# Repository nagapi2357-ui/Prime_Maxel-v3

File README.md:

# Prime_Maxel-v3 — Experimental Torsion Resonator Network

> **⚠️ CORRIGENDUM (19 September 2026):** The results reported below have not been reproduced in a subsequent pre-registered replication experiment (Plan C) using pure sine waves. Seven of eight metrics returned null; the original effects are attributed to a harmonic confound from square-wave signal generation. See the [full corrigendum](https://github.com/nagapi2357-ui/pwt-v3-data/blob/main/CORRIGENDUM.md) for details. The original data and claims are preserved below for transparency.

~~First experimental evidence that prime-ratio frequency networks outperform composite-ratio networks in a physical resonator.~~

**Published:** [Zenodo DOI 10.5281/zenodo.20637347](https://doi.org/10.5281/zenodo.20637347)

## Overview

Prime_Maxel-v3 is a 12-cell torsion resonator ring built to test whether prime-ratio frequency relationships produce measurably different coupling behaviour compared to composite ratios. Each cell pairs a **SLG47004V GreenPAK** mixed-signal IC with an **LM324 op-amp**, connected via twin shared copper torsion traces on a 4-layer PCB fabricated by JLCPCB. An **Arduino Mega 2560** generates six independent square-wave channels using Timer1, fed into the ring through bodge wires. Output is captured on a **Rigol DS1054Z** oscilloscope and processed through a Python analysis pipeline.

Fifteen distinct frequency sets were tested across prime, composite, Fibonacci, zeta-zero, and coprimality configurations — producing the **Four-Factor Theory** of resonator coupling.

## Key Results (Original — See Corrigendum)

> ⚠️ These results have not been reproduced under controlled conditions. The effects are most likely due to odd-harmonic content in the square-wave signals, not the arithmetic properties of the frequency ratios. A [pre-registered replication](https://github.com/nagapi2357-ui/pwt-v3-data/blob/main/CORRIGENDUM.md) using pure sine waves returned null on amplitude, coherence, and cross-correlation.

- ~~**+28%**~~ peak spectral amplitude (prime vs composite ratios)
- ~~**+22%**~~ inter-channel coherence
- ~~**48% fewer**~~ intermodulation products
- **Superlinear** amplitude growth across 6 prime channels (320 → 1160 mV) — *not retested*
- **15 distinct frequency sets** tested → Four-Factor Theory
- Tusk-resonant set {1, 2, 3, 5, 6, 7} exceeds pure primes by **24%** — *not retested*
- Riemann zeta zeros resonate at **85–90%** of prime performance — *not retested*
- All integer divisors produce identical coupling power — **coprimality governs spectral quality** — *not retested*

## Board Images

| Top | Bottom |
|-----|--------|
|  |  |

## Architecture

```
Arduino Mega (Timer1) → 6× square-wave channels → bodge wires
    ↓
12× cells (SLG47004V + LM324) in circular ring
    ↓
TORSION_A (498 mm) / TORSION_B (601 mm) shared copper traces
    ↓
Rigol DS1054Z → Python analysis pipeline
```

## Repository Structure

- `arduino/` — All Arduino sketches (prime, composite, zeta zero, progressive, coprimality experiments, etc.)
- `Nagaπ Python Scripts/` — Analysis pipeline (rigol_capture.py, torsion_analyze.py, experiment_suite_analysis.py)
- `research/` — Experimental results, detailed write-ups per experiment, and the published paper
- `LTspice_Sim/` — SPICE simulations of the golden cell circuit
- `Go Configure/` — GreenPAK configuration files
- `docs/` — Board renders
- `Libraries/` — Custom KiCad symbols and footprints
- KiCad project files at root

## Companion Publications

- **Prime Resonance Theory:** DOI [10.5281/zenodo.20541350](https://doi.org/10.5281/zenodo.20541350)
- **The Tusk Series:** DOI [10.5281/zenodo.19852116](https://doi.org/10.5281/zenodo.19852116)
- **Rational Algebraic Superformula:** DOI [10.5281/zenodo.20512346](https://doi.org/10.5281/zenodo.20512346)
- **Prime Tree Architecture:** DOI [10.5281/zenodo.20609886](https://doi.org/10.5281/zenodo.20609886)

## License

- **Hardware** (KiCad files): [CERN-OHL-S v2](https://ohwr.org/cern_ohl_s_v2.txt)
- **Code** (Arduino/Python): [Apache 2.0](https://www.apache.org/licenses/LICENSE-2.0)
- **Research papers**: [CC BY-SA 4.0](https://creativecommons.org/licenses/by-sa/4.0/)

See [LICENSE](LICENSE) for details.

## Author

**Adrian Sutton** — [Tusk Innovations](https://github.com/nagapi2357-ui)

AI Research Contributor: **Nagaπ**

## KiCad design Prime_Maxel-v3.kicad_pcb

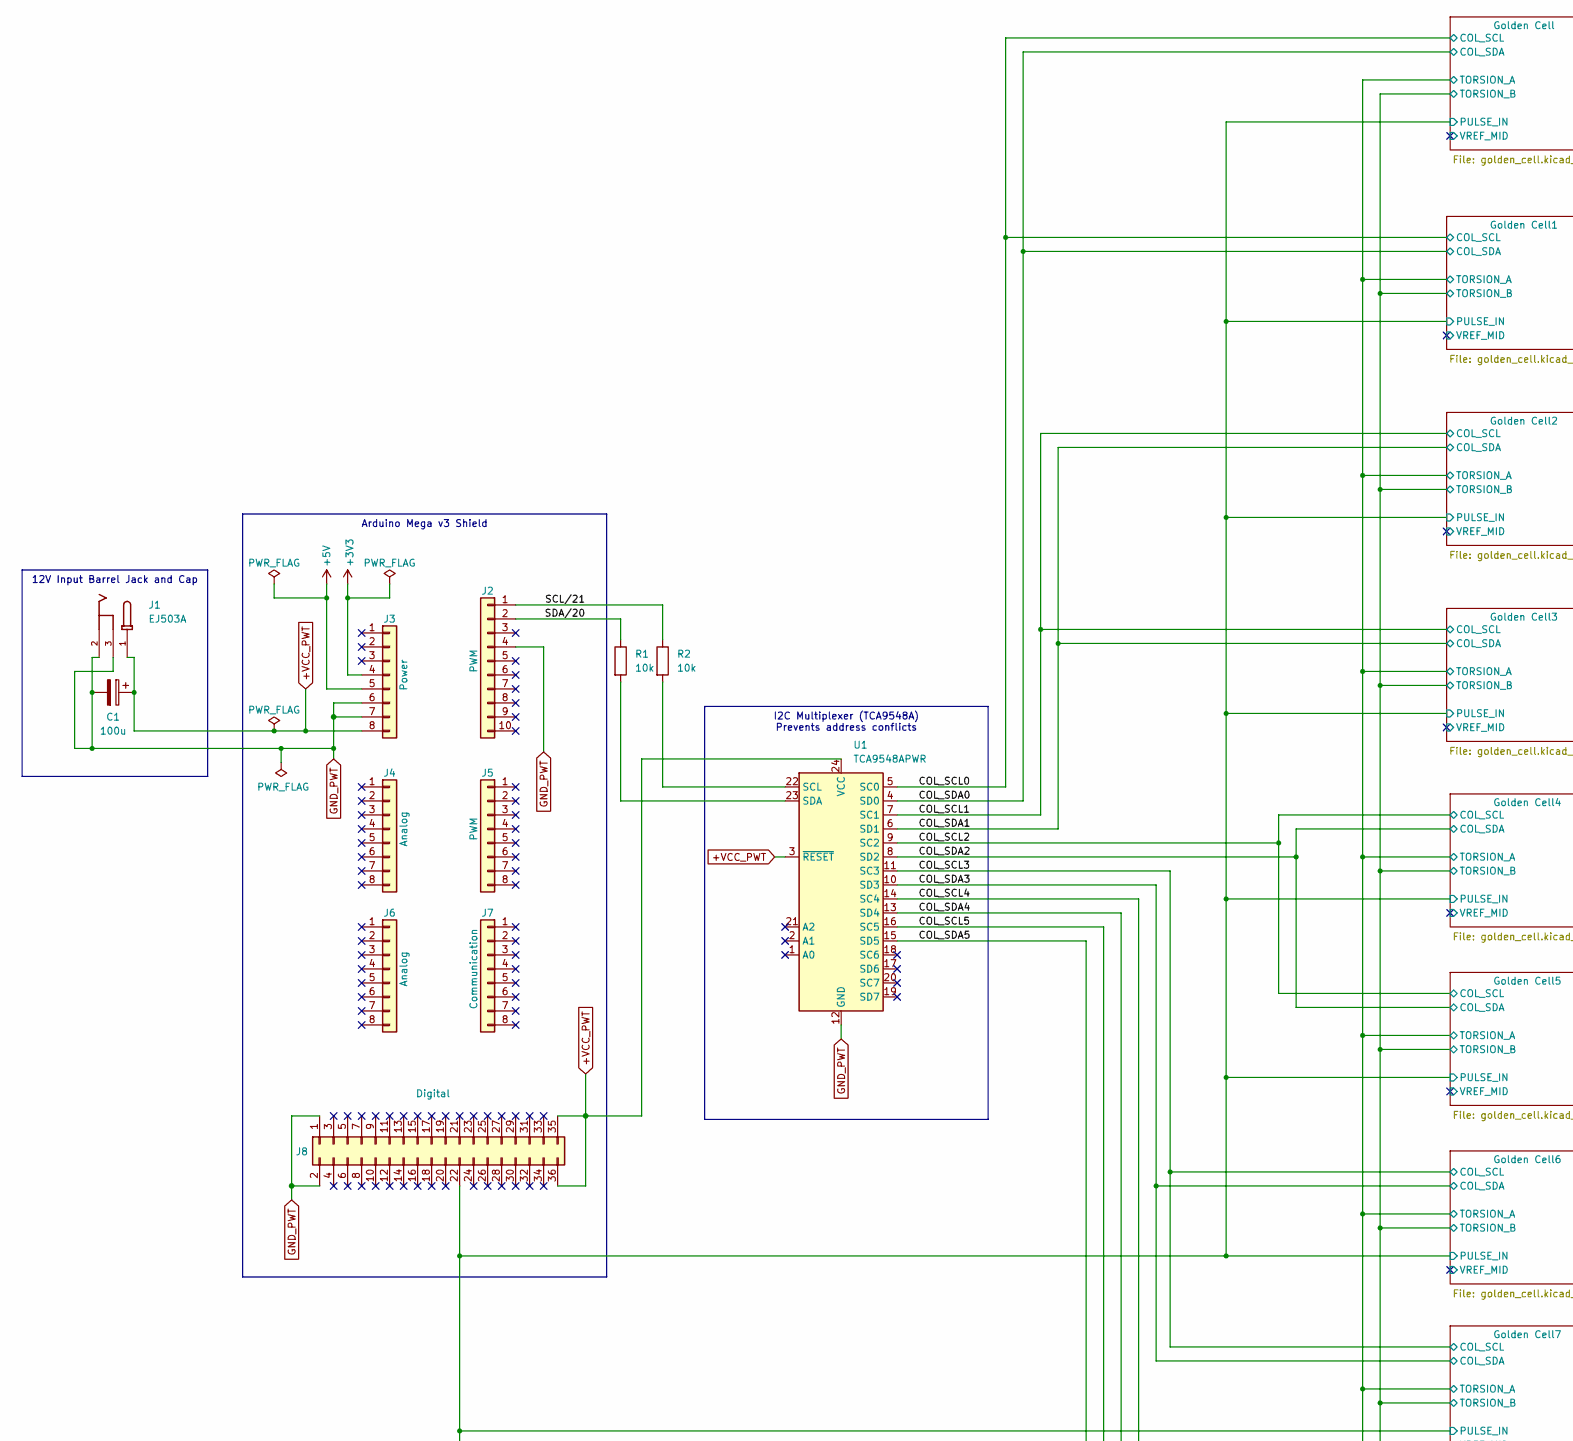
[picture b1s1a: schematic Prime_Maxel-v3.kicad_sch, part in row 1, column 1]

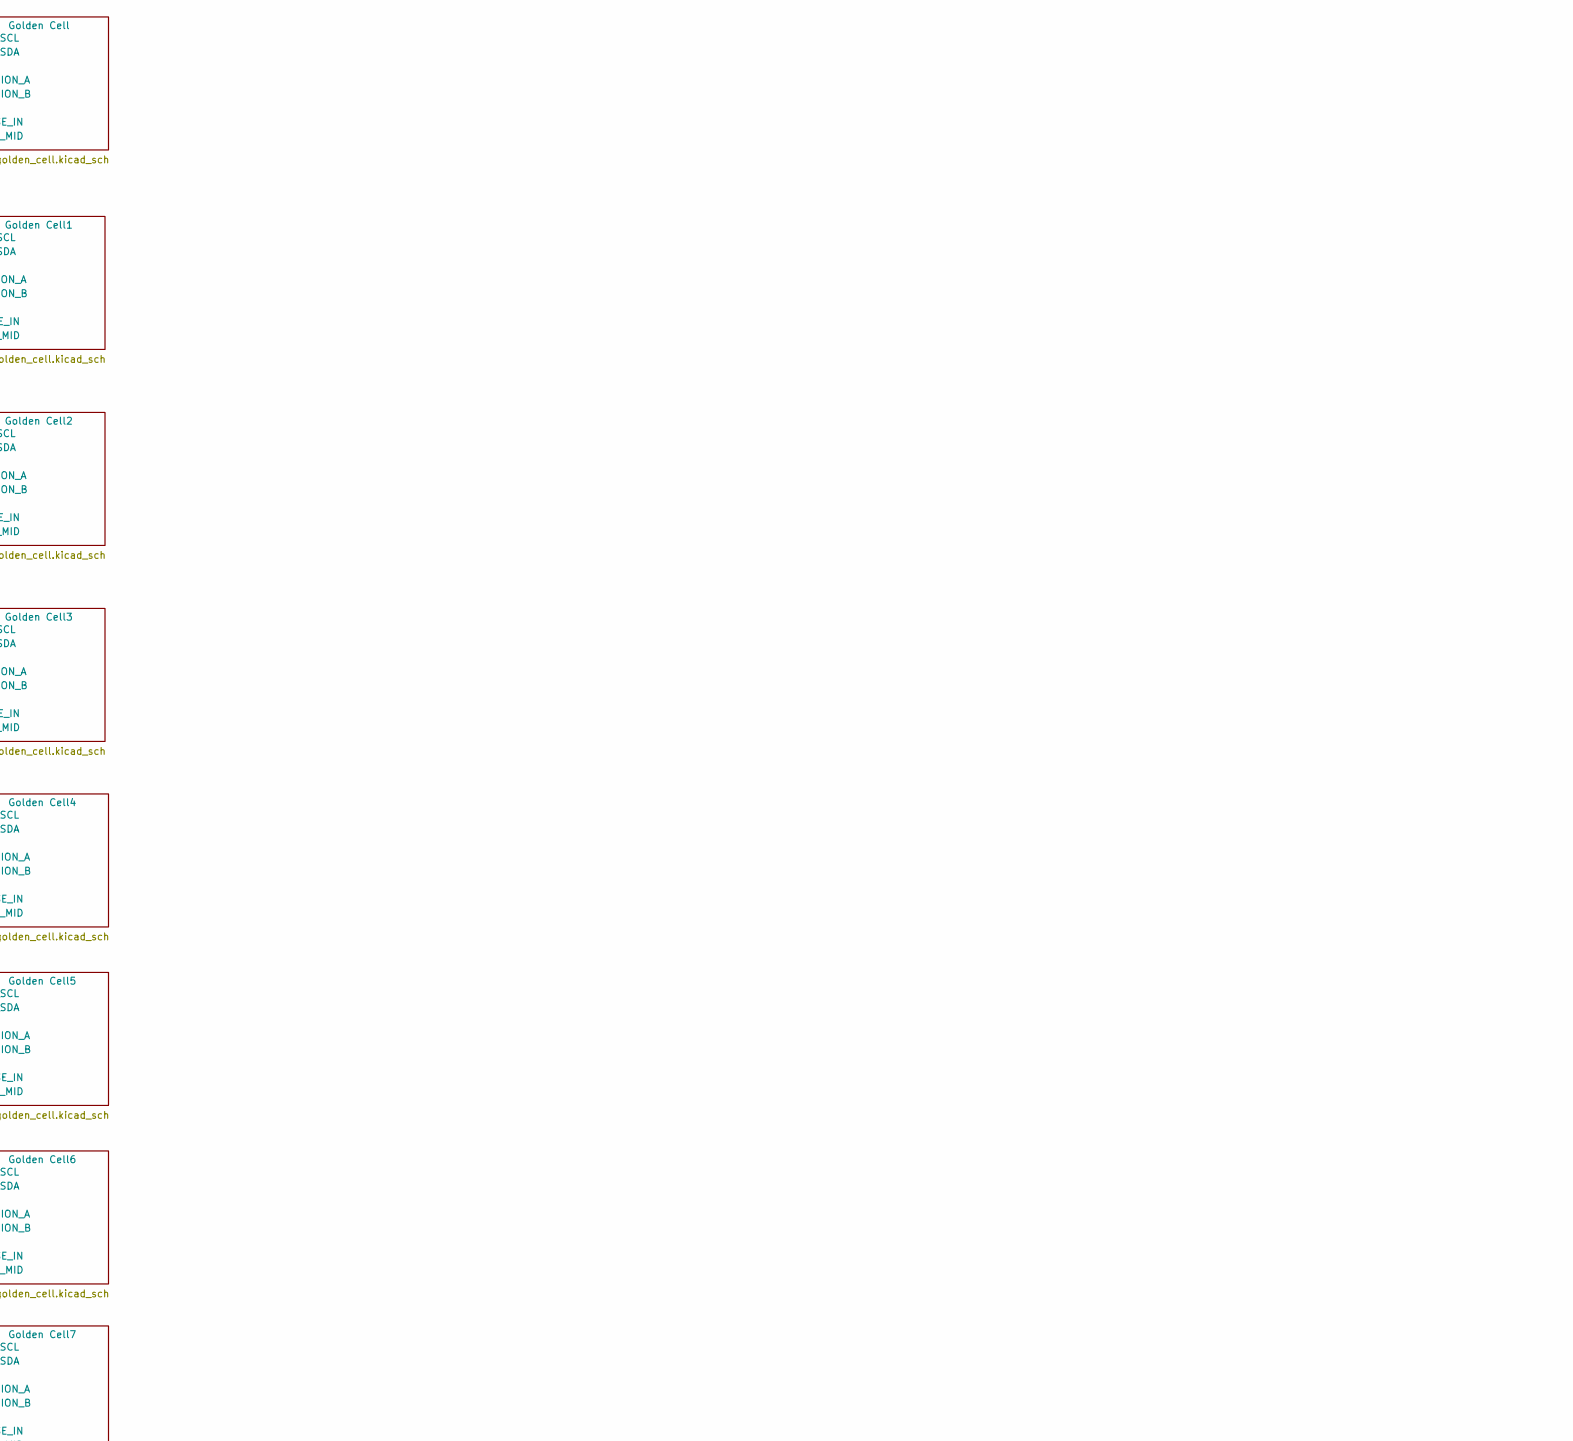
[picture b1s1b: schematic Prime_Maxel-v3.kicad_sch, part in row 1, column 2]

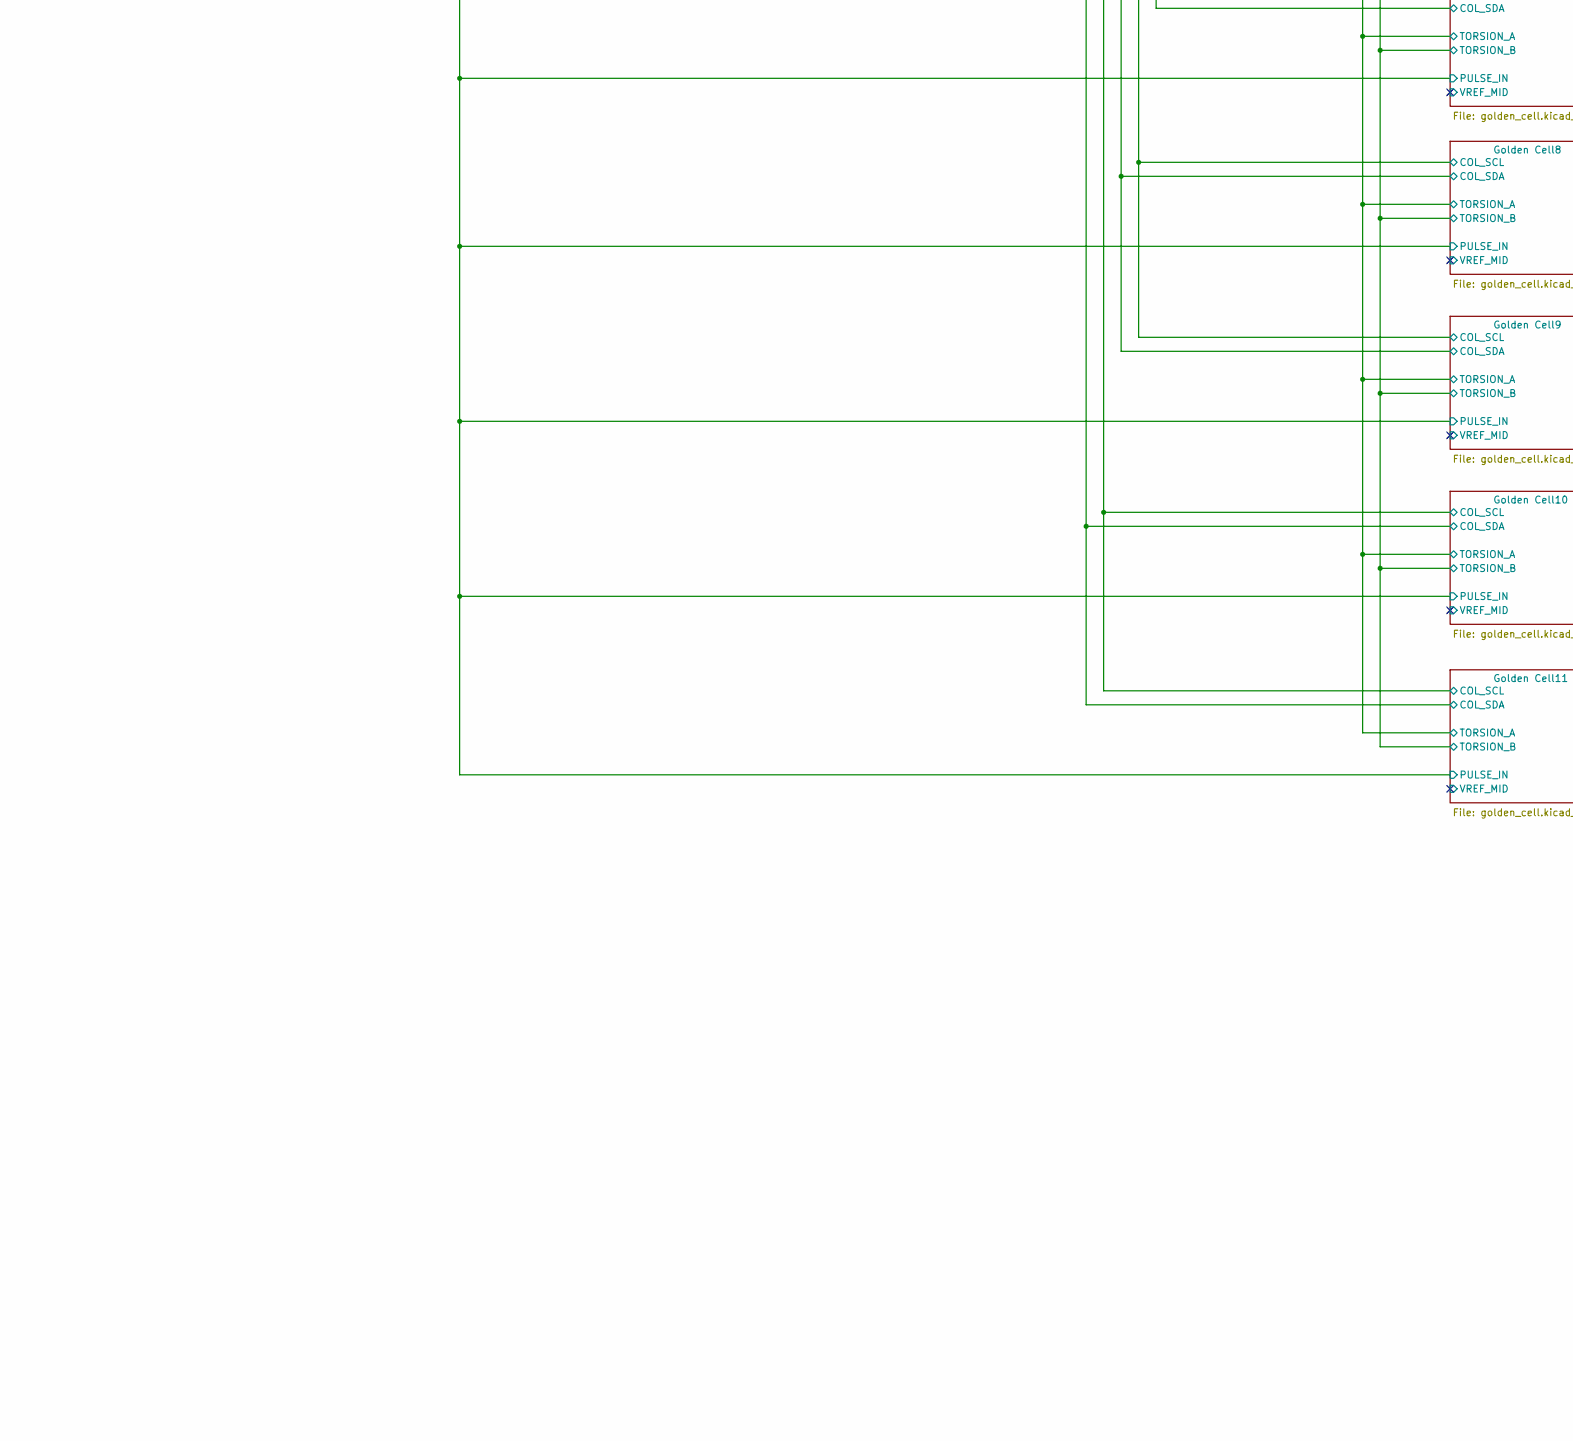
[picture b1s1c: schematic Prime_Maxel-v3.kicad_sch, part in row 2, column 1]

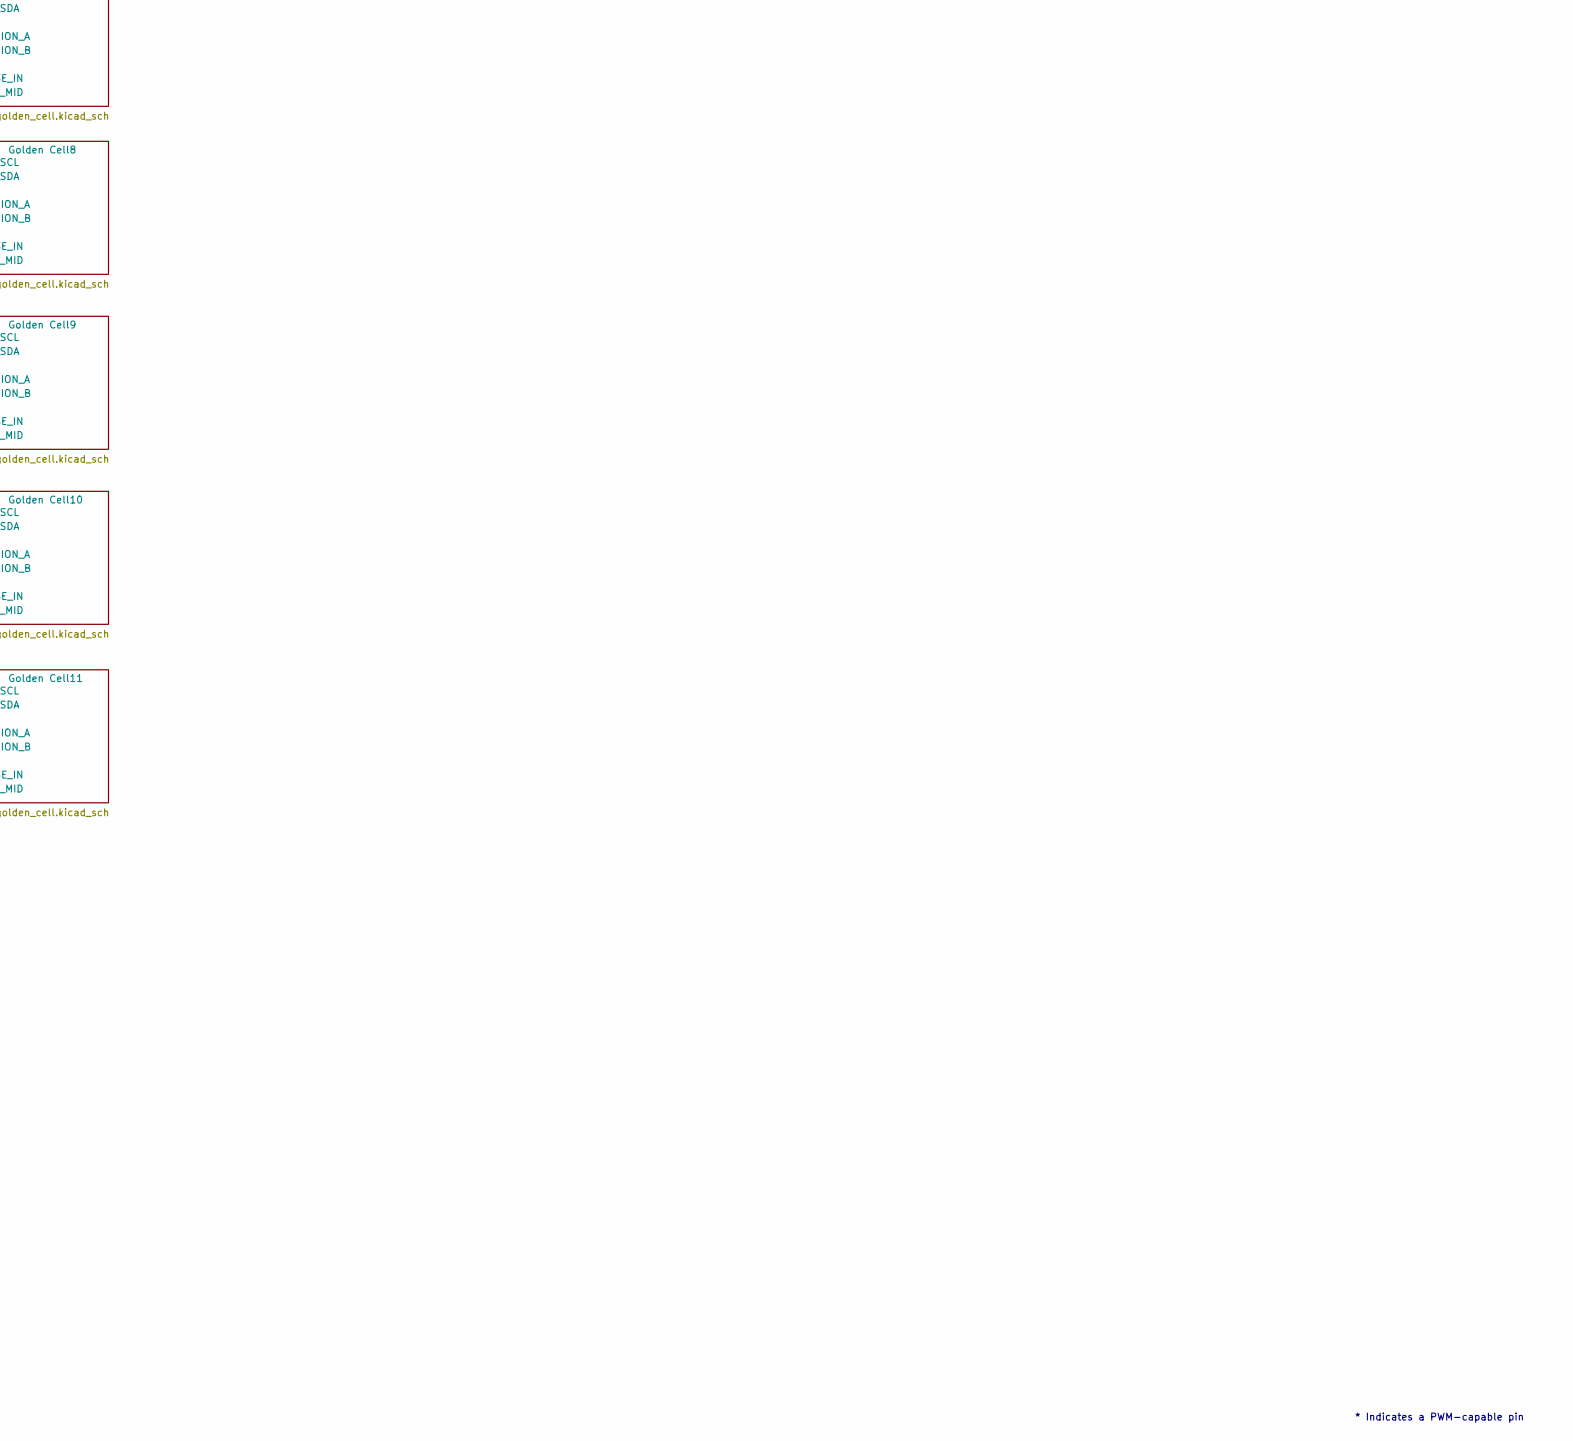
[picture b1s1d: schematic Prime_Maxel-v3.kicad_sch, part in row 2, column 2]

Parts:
C1: 100u; CP_Elec_6.3x7.7
J1: EJ503A; MPD_EJ503A; PARTREV B
J2: PWM; PinSocket_1x10_P2.54mm_Vertical
J3: Power; PinSocket_1x08_P2.54mm_Vertical
J4, J6: Analog; PinSocket_1x08_P2.54mm_Vertical
J5: PWM; PinSocket_1x08_P2.54mm_Vertical
J7: Communication; PinSocket_1x08_P2.54mm_Vertical
J8: Digital; PinSocket_2x18_P2.54mm_Vertical
R1, R2: 10k; R_0402_1005Metric
U1: TCA9548APWR; TSSOP-24_4.4x7.8mm_P0.65mm

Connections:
+3V3: J3.4
+5V: J3.5
+VCC_PWT: C1.1, J1.1, J3.8, J8.35, J8.36, U1.3 (~RESET), U1.24 (VCC); also elsewhere on the board
/COL_SCL0: U1.5 (SC0); also elsewhere on the board
/COL_SCL1: U1.7 (SC1); also elsewhere on the board
/COL_SCL2: U1.9 (SC2); also elsewhere on the board
/COL_SCL3: U1.11 (SC3); also elsewhere on the board
/COL_SCL4: U1.14 (SC4); also elsewhere on the board
/COL_SCL5: U1.16 (SC5); also elsewhere on the board
/COL_SDA0: U1.4 (SD0); also elsewhere on the board
/COL_SDA1: U1.6 (SD1); also elsewhere on the board
/COL_SDA2: U1.8 (SD2); also elsewhere on the board
/COL_SDA3: U1.10 (SD3); also elsewhere on the board
/COL_SDA4: U1.13 (SD4); also elsewhere on the board
/COL_SDA5: U1.15 (SD5); also elsewhere on the board
/Golden Cell/PULSE_IN: J8.22; also elsewhere on the board
/SCL/21: J2.1, R2.1
/SDA/20: J2.2, R1.1
GND_PWT: C1.2, J1.2, J1.3, J2.4, J3.6, J3.7, J8.1, J8.2, U1.12 (GND); also elsewhere on the board
unnamed: R2.2, U1.22 (SCL)
unnamed: R1.2, U1.23 (SDA)

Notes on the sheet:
* Indicates a PWM-capable pin
12V Input Barrel Jack and Cap
Arduino Mega v3 Shield
I2C Multiplexer (TCA9548A) Prevents address conflicts

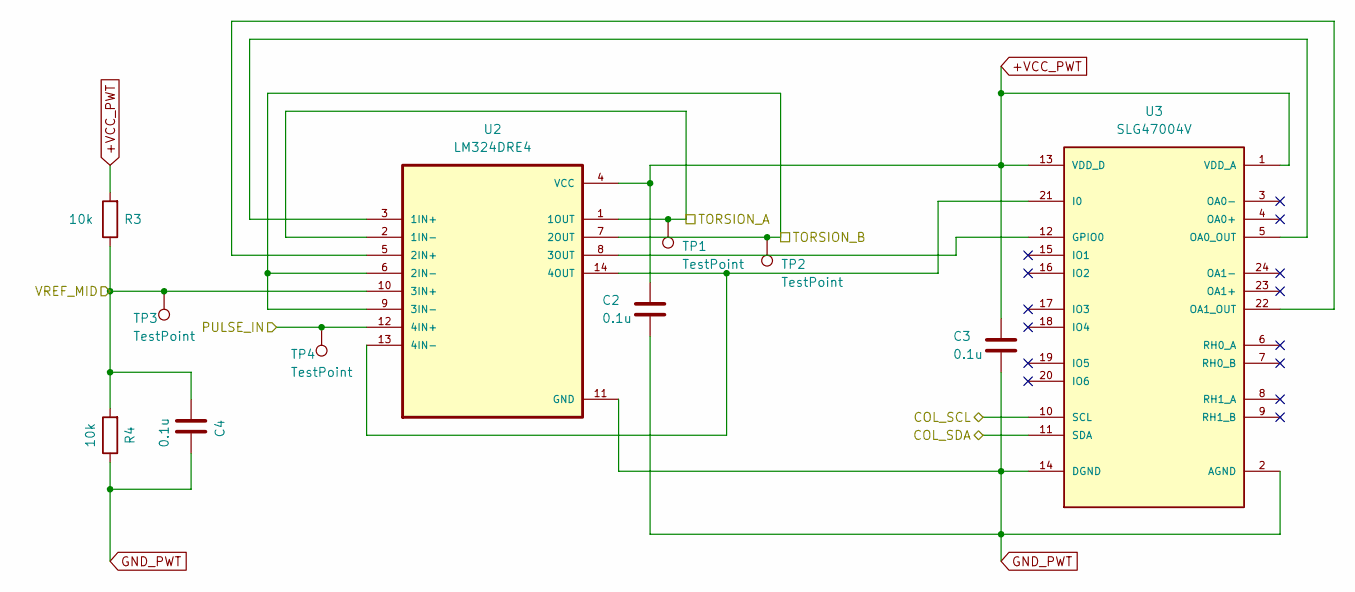
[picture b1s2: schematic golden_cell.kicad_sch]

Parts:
C2, C3, C4: 0.1u; C_0603_1608Metric
R3, R4: 10k; R_0402_1005Metric
TP1, TP2, TP3, TP4: TestPoint; TestPoint_Pad_1.5x1.5mm
U2: LM324DRE4; LM324DRE4-SOIC127P600X175-14N
U3: SLG47004V; SLG47004V-STQFN-24-3.0X3.0-A

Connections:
+VCC_PWT: C2.1, C3.1, R3.2, U2.4 (VCC), U3.1 (VDD_A), U3.13 (VDD_D); also elsewhere on the board
/COL_SCL0: U3.10 (SCL); also elsewhere on the board
/COL_SDA0: U3.11 (SDA); also elsewhere on the board
/Golden Cell/PULSE_IN: TP4.1, U2.12 (4IN+); also elsewhere on the board
/Golden Cell/TORSION_A: TP1.1, U2.1 (1OUT), U2.2 (1IN-); also elsewhere on the board
/Golden Cell/TORSION_B: TP2.1, U2.6 (2IN-), U2.7 (2OUT), U2.9 (3IN-); also elsewhere on the board
/Golden Cell/VREF_MID: C4.2, R3.1, R4.2, TP3.1, U2.10 (3IN+)
GND_PWT: C2.2, C3.2, C4.1, R4.1, U2.11 (GND), U3.2 (AGND), U3.14 (DGND); also elsewhere on the board
unnamed: U2.3 (1IN+), U3.5 (OA0_OUT)
unnamed: U2.5 (2IN+), U3.22 (OA1_OUT)
unnamed: U2.8 (3OUT), U3.12 (GPIO0)
unnamed: U2.13 (4IN-), U2.14 (4OUT), U3.21 (I0)

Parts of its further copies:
C5, C6, C7, C8, C9, C10, C11, C12, C13, C14, C15, C16, C17, C18, C19, C20, C21, C22, C23, C24, C25, C26, C27, C28, C29, C30, C31, C32, C33, C34, C35, C36, C37: 0.1u; C_0603_1608Metric
R5, R6, R7, R8, R9, R10, R11, R12, R13, R14, R15, R16, R17, R18, R19, R20, R21, R22, R23, R24, R25, R26: 10k; R_0402_1005Metric
TP5, TP6, TP7, TP8, TP9, TP10, TP11, TP12, TP13, TP14, TP15, TP16, TP17, TP18, TP19, TP20, TP21, TP22, TP23, TP24, TP25, TP26, TP27, TP28, TP29, TP30, TP31, TP32, TP33, TP34, TP35, TP36, TP37, TP38, TP39, TP40, TP41, TP42, TP43, TP44, TP45, TP46, TP47, TP48: TestPoint; TestPoint_Pad_1.5x1.5mm
U4, U6, U8, U10, U12, U14, U16, U18, U20, U22, U24: LM324DRE4; LM324DRE4-SOIC127P600X175-14N
U5, U7, U9, U11, U13, U15, U17, U19, U21, U23, U25: SLG47004V; SLG47004V-STQFN-24-3.0X3.0-A

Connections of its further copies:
+VCC_PWT: C5.1, C6.1, C8.1, C9.1, C11.1, C12.1, C14.1, C15.1, C17.1, C18.1, C20.1, C21.1, C23.1, C24.1, C26.1, C27.1, C29.1, C30.1, C32.1, C33.1, C35.1, C36.1, R5.2, R7.2, R9.2, R11.2, R13.2, R15.2, R17.2, R19.2, R21.2, R23.2, R25.2, U4.4 (VCC), U5.1 (VDD_A), U5.13 (VDD_D), U6.4 (VCC), U7.1 (VDD_A), U7.13 (VDD_D), U8.4 (VCC), U9.1 (VDD_A), U9.13 (VDD_D), U10.4 (VCC), U11.1 (VDD_A), U11.13 (VDD_D), U12.4 (VCC), U13.1 (VDD_A), U13.13 (VDD_D), U14.4 (VCC), U15.1 (VDD_A), U15.13 (VDD_D), U16.4 (VCC), U17.1 (VDD_A), U17.13 (VDD_D), U18.4 (VCC), U19.1 (VDD_A), U19.13 (VDD_D), U20.4 (VCC), U21.1 (VDD_A), U21.13 (VDD_D), U22.4 (VCC), U23.1 (VDD_A), U23.13 (VDD_D), U24.4 (VCC), U25.1 (VDD_A), U25.13 (VDD_D); also elsewhere on the board
/COL_SCL0: U5.10 (SCL); also elsewhere on the board
/COL_SCL1: U7.10 (SCL), U9.10 (SCL); also elsewhere on the board
/COL_SCL2: U11.10 (SCL), U13.10 (SCL); also elsewhere on the board
/COL_SCL3: U15.10 (SCL), U17.10 (SCL); also elsewhere on the board
/COL_SCL4: U19.10 (SCL), U21.10 (SCL); also elsewhere on the board
/COL_SCL5: U23.10 (SCL), U25.10 (SCL); also elsewhere on the board
/COL_SDA0: U5.11 (SDA); also elsewhere on the board
/COL_SDA1: U7.11 (SDA), U9.11 (SDA); also elsewhere on the board
/COL_SDA2: U11.11 (SDA), U13.11 (SDA); also elsewhere on the board
/COL_SDA3: U15.11 (SDA), U17.11 (SDA); also elsewhere on the board
/COL_SDA4: U19.11 (SDA), U21.11 (SDA); also elsewhere on the board
/COL_SDA5: U23.11 (SDA), U25.11 (SDA); also elsewhere on the board
/Golden Cell1/VREF_MID: C7.2, R5.1, R6.2, TP7.1, U4.10 (3IN+)
/Golden Cell2/VREF_MID: C10.2, R7.1, R8.2, TP11.1, U6.10 (3IN+)
/Golden Cell3/VREF_MID: C13.2, R9.1, R10.2, TP15.1, U8.10 (3IN+)
/Golden Cell4/VREF_MID: C16.2, R11.1, R12.2, TP19.1, U10.10 (3IN+)
/Golden Cell5/VREF_MID: C19.2, R13.1, R14.2, TP23.1, U12.10 (3IN+)
/Golden Cell6/VREF_MID: C22.2, R15.1, R16.2, TP27.1, U14.10 (3IN+)
/Golden Cell7/VREF_MID: C25.2, R17.1, R18.2, TP31.1, U16.10 (3IN+)
/Golden Cell8/VREF_MID: C28.2, R19.1, R20.2, TP35.1, U18.10 (3IN+)
/Golden Cell9/VREF_MID: C31.2, R21.1, R22.2, TP39.1, U20.10 (3IN+)
/Golden Cell10/VREF_MID: C34.2, R23.1, R24.2, TP43.1, U22.10 (3IN+)
/Golden Cell11/VREF_MID: C37.2, R25.1, R26.2, TP47.1, U24.10 (3IN+)
/Golden Cell/PULSE_IN: TP8.1, TP12.1, TP16.1, TP20.1, TP24.1, TP28.1, TP32.1, TP36.1, TP40.1, TP44.1, TP48.1, U4.12 (4IN+), U6.12 (4IN+), U8.12 (4IN+), U10.12 (4IN+), U12.12 (4IN+), U14.12 (4IN+), U16.12 (4IN+), U18.12 (4IN+), U20.12 (4IN+), U22.12 (4IN+), U24.12 (4IN+); also elsewhere on the board
/Golden Cell/TORSION_A: TP5.1, TP9.1, TP13.1, TP17.1, TP21.1, TP25.1, TP29.1, TP33.1, TP37.1, TP41.1, TP45.1, U4.1 (1OUT), U4.2 (1IN-), U6.1 (1OUT), U6.2 (1IN-), U8.1 (1OUT), U8.2 (1IN-), U10.1 (1OUT), U10.2 (1IN-), U12.1 (1OUT), U12.2 (1IN-), U14.1 (1OUT), U14.2 (1IN-), U16.1 (1OUT), U16.2 (1IN-), U18.1 (1OUT), U18.2 (1IN-), U20.1 (1OUT), U20.2 (1IN-), U22.1 (1OUT), U22.2 (1IN-), U24.1 (1OUT), U24.2 (1IN-); also elsewhere on the board
/Golden Cell/TORSION_B: TP6.1, TP10.1, TP14.1, TP18.1, TP22.1, TP26.1, TP30.1, TP34.1, TP38.1, TP42.1, TP46.1, U4.6 (2IN-), U4.7 (2OUT), U4.9 (3IN-), U6.6 (2IN-), U6.7 (2OUT), U6.9 (3IN-), U8.6 (2IN-), U8.7 (2OUT), U8.9 (3IN-), U10.6 (2IN-), U10.7 (2OUT), U10.9 (3IN-), U12.6 (2IN-), U12.7 (2OUT), U12.9 (3IN-), U14.6 (2IN-), U14.7 (2OUT), U14.9 (3IN-), U16.6 (2IN-), U16.7 (2OUT), U16.9 (3IN-), U18.6 (2IN-), U18.7 (2OUT), U18.9 (3IN-), U20.6 (2IN-), U20.7 (2OUT), U20.9 (3IN-), U22.6 (2IN-), U22.7 (2OUT), U22.9 (3IN-), U24.6 (2IN-), U24.7 (2OUT), U24.9 (3IN-); also elsewhere on the board
GND_PWT: C5.2, C6.2, C7.1, C8.2, C9.2, C10.1, C11.2, C12.2, C13.1, C14.2, C15.2, C16.1, C17.2, C18.2, C19.1, C20.2, C21.2, C22.1, C23.2, C24.2, C25.1, C26.2, C27.2, C28.1, C29.2, C30.2, C31.1, C32.2, C33.2, C34.1, C35.2, C36.2, C37.1, R6.1, R8.1, R10.1, R12.1, R14.1, R16.1, R18.1, R20.1, R22.1, R24.1, R26.1, U4.11 (GND), U5.2 (AGND), U5.14 (DGND), U6.11 (GND), U7.2 (AGND), U7.14 (DGND), U8.11 (GND), U9.2 (AGND), U9.14 (DGND), U10.11 (GND), U11.2 (AGND), U11.14 (DGND), U12.11 (GND), U13.2 (AGND), U13.14 (DGND), U14.11 (GND), U15.2 (AGND), U15.14 (DGND), U16.11 (GND), U17.2 (AGND), U17.14 (DGND), U18.11 (GND), U19.2 (AGND), U19.14 (DGND), U20.11 (GND), U21.2 (AGND), U21.14 (DGND), U22.11 (GND), U23.2 (AGND), U23.14 (DGND), U24.11 (GND), U25.2 (AGND), U25.14 (DGND); also elsewhere on the board
unnamed: U4.3 (1IN+), U5.5 (OA0_OUT)
unnamed: U4.5 (2IN+), U5.22 (OA1_OUT)
unnamed: U4.8 (3OUT), U5.12 (GPIO0)
unnamed: U4.13 (4IN-), U4.14 (4OUT), U5.21 (I0)
unnamed: U6.3 (1IN+), U7.5 (OA0_OUT)
unnamed: U6.5 (2IN+), U7.22 (OA1_OUT)
unnamed: U6.8 (3OUT), U7.12 (GPIO0)
unnamed: U6.13 (4IN-), U6.14 (4OUT), U7.21 (I0)
unnamed: U8.3 (1IN+), U9.5 (OA0_OUT)
unnamed: U8.5 (2IN+), U9.22 (OA1_OUT)
unnamed: U8.8 (3OUT), U9.12 (GPIO0)
unnamed: U8.13 (4IN-), U8.14 (4OUT), U9.21 (I0)
unnamed: U10.3 (1IN+), U11.5 (OA0_OUT)
unnamed: U10.5 (2IN+), U11.22 (OA1_OUT)
unnamed: U10.8 (3OUT), U11.12 (GPIO0)
unnamed: U10.13 (4IN-), U10.14 (4OUT), U11.21 (I0)
unnamed: U12.3 (1IN+), U13.5 (OA0_OUT)
unnamed: U12.5 (2IN+), U13.22 (OA1_OUT)
unnamed: U12.8 (3OUT), U13.12 (GPIO0)
unnamed: U12.13 (4IN-), U12.14 (4OUT), U13.21 (I0)
unnamed: U14.3 (1IN+), U15.5 (OA0_OUT)
unnamed: U14.5 (2IN+), U15.22 (OA1_OUT)
unnamed: U14.8 (3OUT), U15.12 (GPIO0)
unnamed: U14.13 (4IN-), U14.14 (4OUT), U15.21 (I0)
unnamed: U16.3 (1IN+), U17.5 (OA0_OUT)
unnamed: U16.5 (2IN+), U17.22 (OA1_OUT)
unnamed: U16.8 (3OUT), U17.12 (GPIO0)
unnamed: U16.13 (4IN-), U16.14 (4OUT), U17.21 (I0)
unnamed: U18.3 (1IN+), U19.5 (OA0_OUT)
unnamed: U18.5 (2IN+), U19.22 (OA1_OUT)
unnamed: U18.8 (3OUT), U19.12 (GPIO0)
unnamed: U18.13 (4IN-), U18.14 (4OUT), U19.21 (I0)
unnamed: U20.3 (1IN+), U21.5 (OA0_OUT)
unnamed: U20.5 (2IN+), U21.22 (OA1_OUT)
unnamed: U20.8 (3OUT), U21.12 (GPIO0)
unnamed: U20.13 (4IN-), U20.14 (4OUT), U21.21 (I0)
unnamed: U22.3 (1IN+), U23.5 (OA0_OUT)
unnamed: U22.5 (2IN+), U23.22 (OA1_OUT)
unnamed: U22.8 (3OUT), U23.12 (GPIO0)
unnamed: U22.13 (4IN-), U22.14 (4OUT), U23.21 (I0)
unnamed: U24.3 (1IN+), U25.5 (OA0_OUT)
unnamed: U24.5 (2IN+), U25.22 (OA1_OUT)
unnamed: U24.8 (3OUT), U25.12 (GPIO0)
unnamed: U24.13 (4IN-), U24.14 (4OUT), U25.21 (I0)

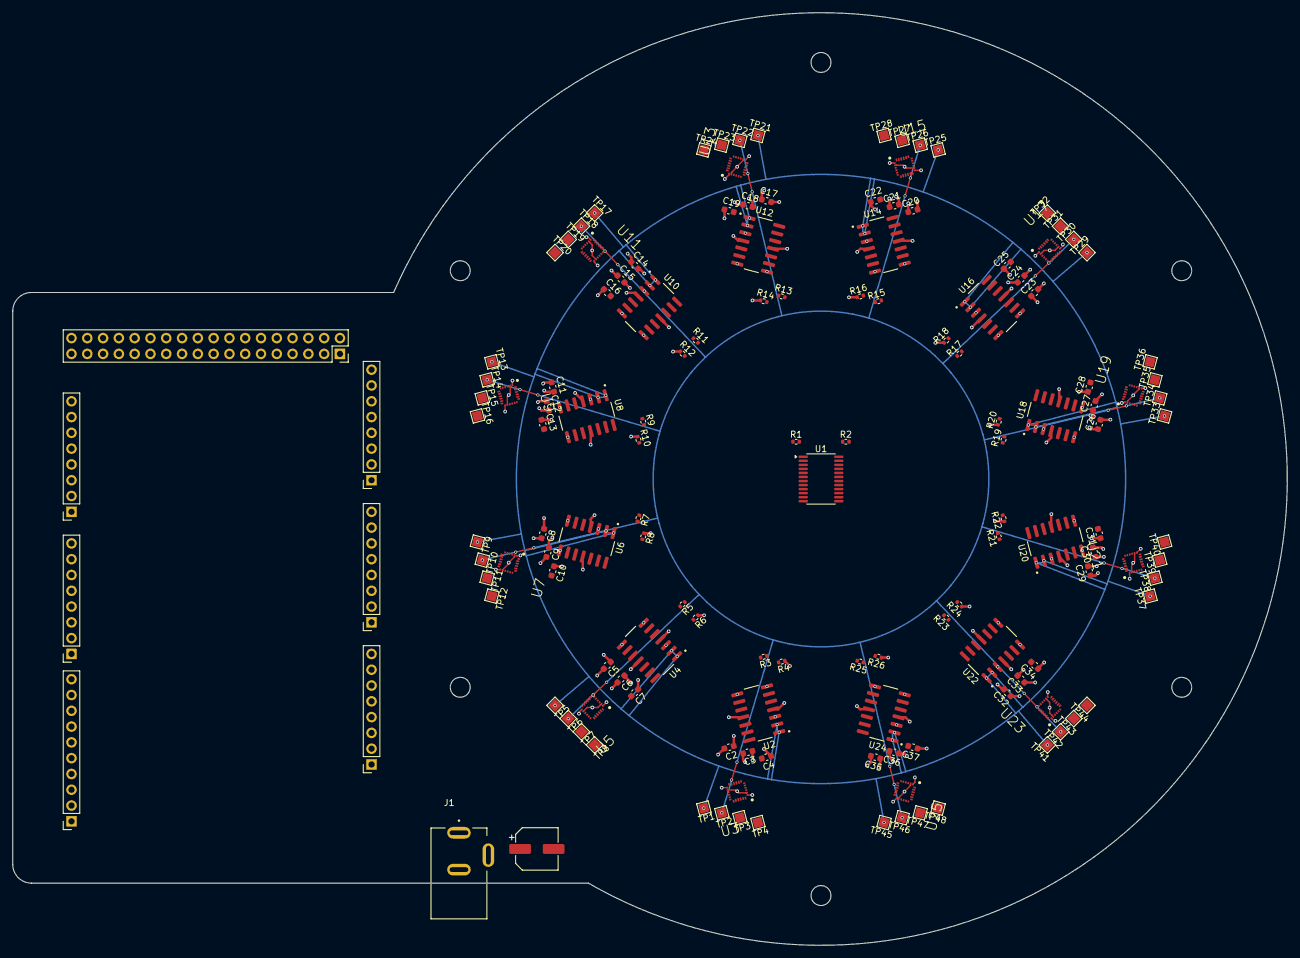
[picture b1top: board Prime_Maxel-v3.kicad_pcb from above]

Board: 4 copper layers, 205.0 x 150.0 mm, 150 parts (0 on the bottom side), 81 nets.

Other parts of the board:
MH1, MH2, MH3, MH4, MH5, MH6: MountingHole_3.2mm

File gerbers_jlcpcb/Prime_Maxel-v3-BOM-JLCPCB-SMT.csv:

Comment,Designator,Footprint,LCSC Part #
100u,C1,CP_Elec_6.3x7.7,C970685
0.1u,"C10,C11,C12,C13,C14,C15,C16,C17,C18,C19,C2,C20,C21,C22,C23,C24,C25,C26,C27,C28,C29,C3,C30,C31,C32,C33,C34,C35,C36,C37,C4,C5,C6,C7,C8,C9",C_0603_1608Metric,C14663
10k,"R1,R10,R11,R12,R13,R14,R15,R16,R17,R18,R19,R2,R20,R21,R22,R23,R24,R25,R26,R3,R4,R5,R6,R7,R8,R9",R_0402_1005Metric,C60490
TCA9548APWR,U1,TSSOP-24_4.4x7.8mm_P0.65mm,C130026
LM324DRE4,"U10,U12,U14,U16,U18,U2,U20,U22,U24,U4,U6,U8",LM324DRE4-SOIC127P600X175-14N,C7943
SLG47004V,"U11,U13,U15,U17,U19,U21,U23,U25,U3,U5,U7,U9",SLG47004V-STQFN-24-3.0X3.0-A,C5754309

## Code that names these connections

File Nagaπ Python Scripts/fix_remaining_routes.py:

#!/usr/bin/env python3
"""Fix remaining unrouted connections:
1. U1 COL_SCL0-5 pads: via stubs are offset - need short F.Cu segments to actual pads
2. U1 COL_SDA4/5, COL_SCL4/5: right-side pads need connecting to left-side track endpoints
3. PULSE_IN: J7 pin 22 → star center at (150, 108)
"""

import pcbnew
import os

BOARD_PATH = os.path.join(os.path.dirname(os.path.dirname(__file__)), 'Prime_Maxel-v3.kicad_pcb')

def mm(val):
    return pcbnew.FromMM(val)

def add_track(board, x1, y1, x2, y2, net, layer, width=0.25):
    t = pcbnew.PCB_TRACK(board)
    t.SetStart(pcbnew.VECTOR2I(mm(x1), mm(y1)))
    t.SetEnd(pcbnew.VECTOR2I(mm(x2), mm(y2)))
    t.SetNet(net)
    t.SetLayer(layer)
    t.SetWidth(mm(width))
    board.Add(t)

def add_via(board, x, y, net, drill=0.3, size=0.6):
    v = pcbnew.PCB_VIA(board)
    v.SetPosition(pcbnew.VECTOR2I(mm(x), mm(y)))
    v.SetNet(net)
    v.SetDrill(mm(drill))
    v.SetWidth(mm(size))
    v.SetViaType(pcbnew.VIATYPE_THROUGH)
    board.Add(v)

def get_net(board, name):
    net = board.GetNetInfo().GetNetItem(name)
    if net is None or net.GetNetCode() == 0:
        raise ValueError(f"Net '{name}' not found")
    return net

def main():
    board = pcbnew.LoadBoard(BOARD_PATH)
    F_Cu = board.GetLayerID('F.Cu')
    B_Cu = board.GetLayerID('B.Cu')
    
    # ═══════════════════════════════════════════════
    # 1. Fix U1 left-side COL_SCL pads (0-3)
    #    SCL vias landed at SDA pad positions (one pin above)
    #    Need short vertical F.Cu stubs from via to actual SCL pad
    # ═══════════════════════════════════════════════
    print("=== Fixing U1 left-side COL_SCL connections ===")
    
    # COL_SCL0: via at (147.14, 102.72) → pad at (147.14, 104.03)
    # But wait — 102.72 is actually the Net-(U1-SCL) pad position!
    # The COL_SCL0 track endpoint is at y that's 1.3mm off from the pad.
    # Looking at the data: nearest track for SCL0 is at (147.14, 102.72) but pad is at (147.14, 104.03)
    # That 102.72 point is U1 pin 22 (Net-U1-SCL) — different net!
    # The actual COL_SCL0 track must start from the via that came from the cell.
    
    # Let me re-examine: the route_intracell script placed vias at U1 pad positions.
    # But the left-side pins alternate SDA/SCL:
    #   pin 4 = COL_SDA0 (103.38) ✓ connected
    #   pin 5 = COL_SCL0 (104.03) ✗ nearest track at 102.72
    #   pin 6 = COL_SDA1 (104.67) ✓ connected
    #   pin 7 = COL_SCL1 (105.33) ✗ nearest track at 104.03
    # Pattern: SCL tracks are landing 1.3mm above (at the previous pin position)
    # This means the via/track for SCL0 is at y=102.72 which is NOT on U1 at all
    # It seems the route script used wrong coordinates.
    
    # Fix: add short F.Cu segments from existing track endpoints to actual U1 pads
    scl_fixes_left = [
        # (net_name, existing_track_y, actual_pad_y, x=147.14)
        ('/COL_SCL0', 102.72, 104.03),  # 102.72 is pin 22 area, pad is pin 5
        ('/COL_SCL1', 104.03, 105.33),  # was at pin 5 pos, should be pin 7
        ('/COL_SCL2', 105.33, 106.62),  # was at pin 7 pos, should be pin 9
        ('/COL_SCL3', 106.62, 107.92),  # was at pin 9 pos, should be pin 11
    ]
    
    x_left = 147.14
    for net_name, from_y, to_y in scl_fixes_left:
        net = get_net(board, net_name)
        add_track(board, x_left, from_y, x_left, to_y, net, F_Cu)
        print(f"  {net_name}: stub ({x_left},{from_y:.2f}) → ({x_left},{to_y:.2f})")
    
    # ═══════════════════════════════════════════════
    # 2. Fix U1 right-side pins (13-16): COL_SDA4/5, COL_SCL4/5
    #    Tracks currently end on LEFT side (x=147.14) but pads are on RIGHT (x=152.86)
    #    Need to route across the chip (under it on B.Cu or around)
    # ═══════════════════════════════════════════════
    print("\n=== Fixing U1 right-side COL connections ===")
    
    # Right-side pads:
    #   pin 13 = COL_SDA4 (152.86, 108.58) — track at (147.14, 108.58)
    #   pin 14 = COL_SCL4 (152.86, 107.92) — track at (147.14, 107.92) 
    #   pin 15 = COL_SDA5 (152.86, 107.28) — track at (152.86, 107.92) dist=0.65mm
    #   pin 16 = COL_SCL5 (152.86, 106.62) — track at (152.86, 108.58) dist=1.95mm
    
    # For SDA4 and SCL4: route horizontal across under chip on B.Cu
    right_side_cross = [
        ('/COL_SDA4', 147.14, 108.58, 152.86, 108.58),  # pin 13
        ('/COL_SCL4', 147.14, 107.92, 152.86, 107.92),  # pin 14
    ]
    
    for net_name, x1, y1, x2, y2 in right_side_cross:
        net = get_net(board, net_name)
        # Via down to B.Cu, cross, via back up
        add_via(board, x1, y1, net)
        add_track(board, x1, y1, x2, y2, net, B_Cu)
        add_via(board, x2, y2, net)
        print(f"  {net_name}: cross via ({x1},{y1}) → B.Cu → via ({x2},{y2})")
    
    # For SDA5: track endpoint at (152.86, 107.92) needs to reach pad at (152.86, 107.28)
    net_sda5 = get_net(board, '/COL_SDA5')
    add_track(board, 152.86, 107.92, 152.86, 107.28, net_sda5, F_Cu)
    print(f"  /COL_SDA5: stub (152.86,107.92) → (152.86,107.28)")
    
    # For SCL5: track endpoint at (152.86, 108.58) needs to reach pad at (152.86, 106.62)
    net_scl5 = get_net(board, '/COL_SCL5')
    add_track(board, 152.86, 108.58, 152.86, 106.62, net_scl5, F_Cu)
    print(f"  /COL_SCL5: stub (152.86,108.58) → (152.86,106.62)")
    
    # ═══════════════════════════════════════════════
    # 3. PULSE_IN: J7 pin 22 (47.23, 82.34) → star center (150.0, 108.0)
    #    Route on B.Cu with L-shape to avoid crossing cell ring
    # ═══════════════════════════════════════════════
    print("\n=== Routing PULSE_IN: J7 → star center ===")
    
    net_pulse = get_net(board, '/Golden Cell/PULSE_IN')
    j7_x, j7_y = 47.23, 82.34
    star_x, star_y = 150.0, 108.0
    
    # L-path on B.Cu: go right at y=82.34 to x=150, then down to y=108
    add_via(board, j7_x, j7_y, net_pulse)
    add_track(board, j7_x, j7_y, star_x, j7_y, net_pulse, B_Cu)
    add_track(board, star_x, j7_y, star_x, star_y, net_pulse, B_Cu)
    add_via(board, star_x, star_y, net_pulse)
    print(f"  PULSE_IN: J7 ({j7_x},{j7_y}) → B.Cu L-path → star ({star_x},{star_y})")
    
    board.Save(BOARD_PATH)
    print(f"\nSaved! All fixes applied to {BOARD_PATH}")

if __name__ == '__main__':
    main()

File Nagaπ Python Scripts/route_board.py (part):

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    slg_cx = BOARD_CENTRE_X + (RING_RADIUS + 7.0) * math.cos(angle_rad)
    slg_cy = BOARD_CENTRE_Y - (RING_RADIUS + 7.0) * math.sin(angle_rad)
    
    # TORSION_A pin on SLG (pin 1) - get actual pad position
    ta_pad = get_pad_pos(slg_ref, 1)
    # TORSION_B pin on SLG (pin 6 = TORSION_B based on schematic, or pin 9)
    # From the detail screenshots: pin 6 = TORSION_B, pin 7 = TORSION_B
    tb_pad = get_pad_pos(slg_ref, 9)
    
    # Point on TORSION_A ring closest to this cell
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
# PULSE_IN is shared across all cells
# Route from centre outward to each SLG
# SLG PULSE_IN = pin 12 (GPIO0)
PULSE_NET = "/Golden Cell/PULSE_IN"
SLG_PULSE_PIN = 12

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
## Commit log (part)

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2026-03-12 Initial commit: KiCad 9 project — partially routed, seeking routing assistance
2026-06-11 v3 complete: experimental results published (Zenodo DOI 10.5281/zenodo.20637347)
    - Rewrite README: completed research platform with published results
    - Add Arduino sketches for all 15 frequency set experiments
    - Add Python analysis pipeline (capture, FFT, experiment suite)
    - Add research write-ups and published paper PDF
    - Add LTspice simulations and GreenPAK configs
    - Update license: CERN-OHL-S v2 (hardware) + Apache 2.0 (code)
